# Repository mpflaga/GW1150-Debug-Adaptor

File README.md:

# GW1152-USB
Cable/PCB adaptor to provide quick conversion of any VA/GW power supply to Debug of common USB to TTL/3v3 Serial adaptor

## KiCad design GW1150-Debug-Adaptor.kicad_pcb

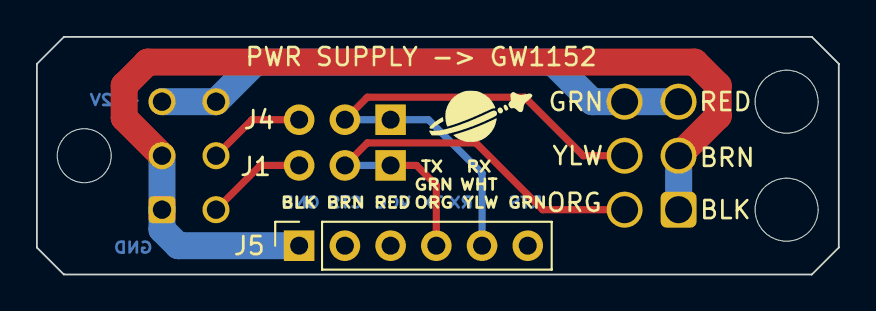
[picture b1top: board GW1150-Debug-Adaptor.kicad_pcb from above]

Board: 2 copper layers, 44.6 x 13.2 mm, 5 parts (1 on the bottom side), 6 nets.

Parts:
J1, J4: SW_SPDT; PinHeader_1x03_P2.54mm_Vertical
J2, J3: Conn_02x03_Counter_Clockwise; Molex_Micro-Fit_3.0_43045-0600_2x03_P3.00mm_Horizontal
J5: Conn_01x06; PinSocket_1x06_P2.54mm_Vertical

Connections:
+12V: J2.3, J2.6, J3.3, J3.6
/RxD_ROUTER: J1.1 (A), J1.2 (B), J3.4, J5.4
/RxD_SUPPLY: J1.3 (C), J2.4
/TxD_ROUTER: J3.5, J4.1 (A), J4.2 (B), J5.5
/TxD_SUPPLY: J2.5, J4.3 (C)
GND: J2.1, J2.2, J3.1, J3.2, J5.1

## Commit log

2023-02-16 Initial commit of v0.1
2023-02-16 v1.0 changes after building initial units. Enlarged drill holes for cable whip. Added shunts across the jumpers, for default use. miscellaneous labeling.
2023-02-16 Add of v0.1 of first purchase
